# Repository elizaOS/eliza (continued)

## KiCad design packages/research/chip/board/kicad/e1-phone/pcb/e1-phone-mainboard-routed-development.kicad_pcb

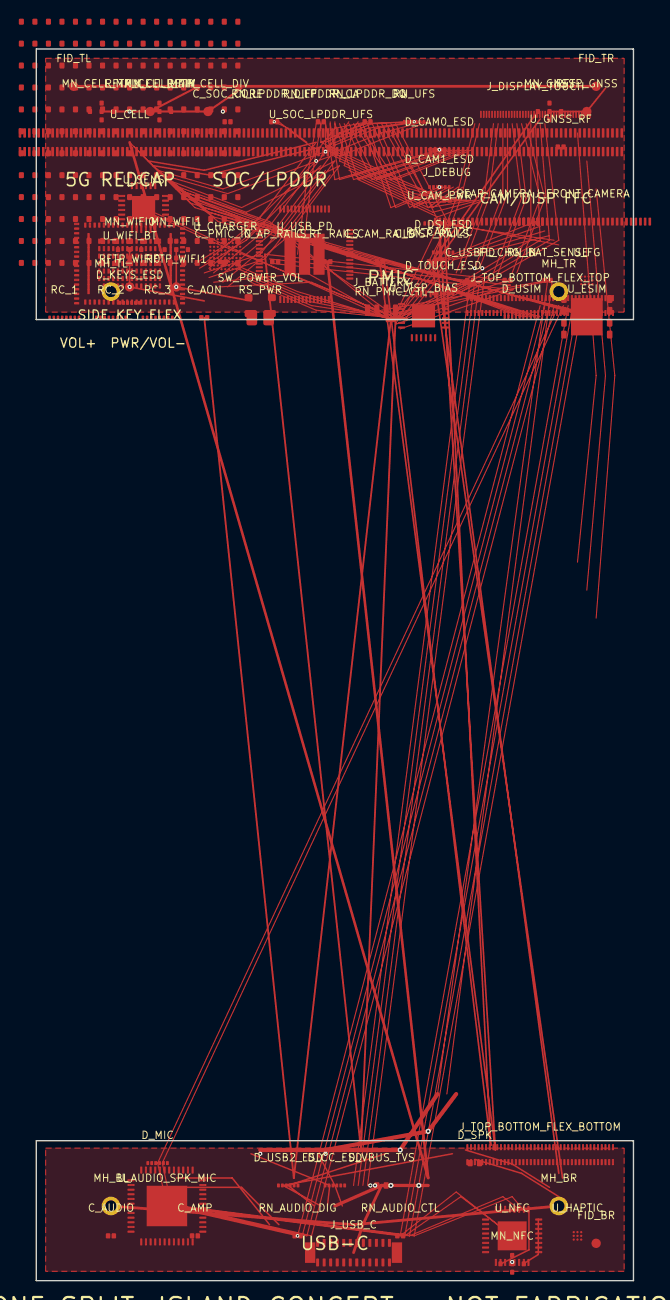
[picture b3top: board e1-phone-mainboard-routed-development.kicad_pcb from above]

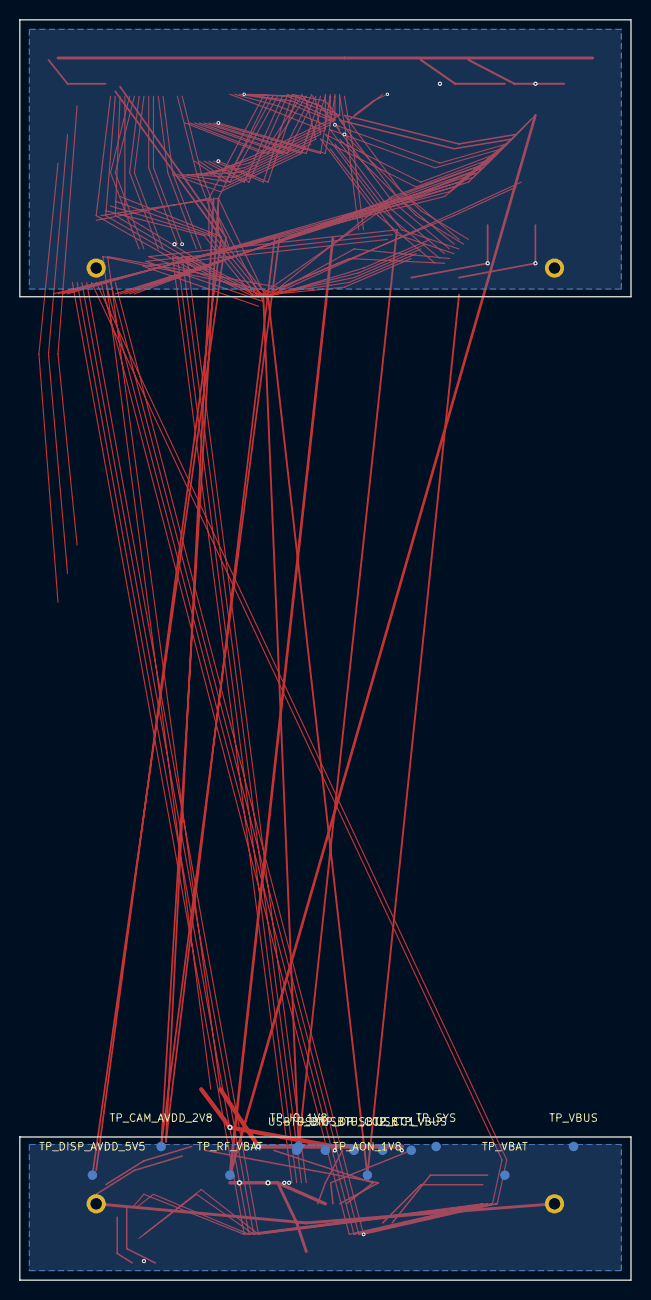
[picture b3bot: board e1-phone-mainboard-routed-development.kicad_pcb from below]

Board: 10 copper layers, 64.0 x 132.0 mm, 89 parts (13 on the bottom side), 109 nets.

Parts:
C_AMP: SMART_AMP_RAIL_DECOUPLING; C0402_DEV
C_AON: AON_BUTTON_WAKE_DECOUPLING; C0402_DEV
C_AP_RAILS: AP_CORE_IO_DECOUPLING; C0402_DEV
C_AUDIO: AUDIO_CODEC_RAIL_DECOUPLING; C0402_DEV
C_CAM_RAILS: CAMERA_AVDD_DVDD_DECOUPLING; C0402_DEV
C_DISP_RAILS: DISPLAY_BIAS_DECOUPLING; C0402_DEV
C_PMIC_IN: PMIC_SYS_VBAT_INPUT_DECOUPLING; C0402_DEV
C_RF_RAILS: RF_VBAT_IO_DECOUPLING; C0402_DEV
C_SOC_CORE: SOC_CORE_IO_DECOUPLING; C0402_DEV
C_USBPD: USBPD_VIN_DECOUPLING; C0402_DEV
D_CAM0_ESD: CAM0_CSI_ESD_ARRAY; ESD_ARRAY_6CH_DEV
D_CAM1_ESD: CAM1_CSI_ESD_ARRAY; ESD_ARRAY_6CH_DEV
D_CC_ESD: CC_ESD_ARRAY; ESD_ARRAY_6CH_DEV
D_DSI_ESD: DSI_4LANE_ESD_ARRAY; ESD_ARRAY_6CH_DEV
D_KEYS_ESD: SIDE_KEY_ESD_ARRAY; ESD_ARRAY_6CH_DEV
D_MIC: PDM_MIC_ESD_BIAS_DEVELOPMENT_PATTERN; ESD_ARRAY_6CH_DEV
D_SPK: SPEAKER_OUTPUT_PROTECT; TVS_DIODE_2P_DEV
D_TOUCH_ESD: TOUCH_CONTROL_ESD; ESD_ARRAY_6CH_DEV
D_USB2_ESD: USB2_ESD_ARRAY; ESD_ARRAY_6CH_DEV
D_USIM: USIM_ESD_LEVEL_SHIFT_DEVELOPMENT_PATTERN; USIM_ESD_LEVELSHIFT_DEV
D_VBUS_TVS: VBUS_TVS; TVS_DIODE_2P_DEV
FID_BR: FIDUCIAL; FIDUCIAL_1MM_DEV
FID_TL: FIDUCIAL; FIDUCIAL_1MM_DEV
FID_TR: FIDUCIAL; FIDUCIAL_1MM_DEV
FL_CHG_IN: VBUS_CHARGER_INPUT_FILTER; C0402_DEV
J_BATTERY: battery_pack_power_thermistor_id; BATTERY_4P_1P00_DEV
J_DEBUG: JTAG_BOOT_STRAP_TEST_ACCESS; R0402_DEV
J_DISPLAY_TOUCH: 5p5_in_fhd_mipi_display_touch_fpc_connector_escape; DISPLAY_40P_0P30_DEV
J_FRONT_CAMERA: 30-pin front MIPI CSI camera FPC development conn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; CAMERA_30P_0P50_DEV
J_REAR_CAMERA: 24-pin rear MIPI CSI camera FPC development conne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; CAMERA_24P_0P50_DEV
J_TOP_BOTTOM_FLEX_BOTTOM: bottom_mate_for_split_board_interconnect; HIROSE_DF40_80P_0P4_DEV
J_TOP_BOTTOM_FLEX_TOP: top_mate_for_split_board_interconnect; HIROSE_DF40_80P_0P4_DEV
J_USB_C: charging_data_debug_single_usb_c_port; GCT_USB4105_GF_A_DEV
MH_BL: MOUNT; MOUNTING_HOLE_1P2_DEV
MH_BR: MOUNT; MOUNTING_HOLE_1P2_DEV
MH_TL: MOUNT; MOUNTING_HOLE_1P2_DEV
MH_TR: MOUNT; MOUNTING_HOLE_1P2_DEV
MN_CELL_DIV: CELL_RF_DIV_PI_MATCH; PI_MATCH_0402_DEV
MN_CELL_MAIN: CELL_RF_MAIN_PI_MATCH; PI_MATCH_0402_DEV
MN_GNSS: CELL_GNSS_RF_PI_MATCH; PI_MATCH_0402_DEV
MN_NFC: NFC_LOOP_MATCH_DEVELOPMENT_PATTERN; NFC_LOOP_MATCH_DEV
MN_WIFI0: WIFI_BT_RF0_PI_MATCH; PI_MATCH_0402_DEV
MN_WIFI1: WIFI_BT_RF1_PI_MATCH; PI_MATCH_0402_DEV
RC_1: PWR_KEY_N_RC_DEBOUNCE; RC_ARRAY_4CH_DEV
RC_2: VOL_UP_N_RC_DEBOUNCE; RC_ARRAY_4CH_DEV
RC_3: VOL_DOWN_N_RC_DEBOUNCE; RC_ARRAY_4CH_DEV
RFTP_CELL_DIV: CELL_RF_DIV; TESTPOINT_1MM_DEV
RFTP_CELL_MAIN: CELL_RF_MAIN; TESTPOINT_1MM_DEV
RFTP_GNSS: CELL_GNSS_RF; TESTPOINT_1MM_DEV
RFTP_WIFI0: WIFI_BT_RF0; TESTPOINT_1MM_DEV
RFTP_WIFI1: WIFI_BT_RF1; TESTPOINT_1MM_DEV
RN_AUDIO_CTL: AUDIO_I2C_IRQ_PULLUPS; R0402_DEV
RN_AUDIO_DIG: I2S_PDM_DAMPING_DEVELOPMENT_PATTERN; R0402_DEV
RN_BAT_SENSE: BATTERY_NTC_ID_SENSE; R0402_DEV
RN_CAM_I2C: CAMERA_I2C_AF_PULLUPS; R0402_DEV
RN_LPDDR_CA: LPDDR_CA_DAMPING_DEVELOPMENT_PATTERN; R0402_DEV
RN_LPDDR_DIFF: LPDDR_CK_DQS_TERM_DEVELOPMENT_PATTERN; R0402_DEV
RN_LPDDR_DQ: LPDDR_DQ_ESCAPE_DEVELOPMENT_PATTERN; R0402_DEV
RN_PMIC_CTL: PMIC_CHARGER_PD_I2C_IRQ_PULLUPS; R0402_DEV
RN_UFS: UFS_MPHY_ESD_TERM_DEVELOPMENT_PATTERN; ESD_ARRAY_6CH_DEV
RS_PWR: VBUS_VBAT_SYS_CURRENT_SENSE; SHUNT_1206_DEV
SW_POWER_VOL: power_volume_side_key_flex_connector; PANASONIC_EVQ_P7_DEV
TP_AON_1V8: AON_1V8; TESTPOINT_1MM_DEV
TP_CAM_AVDD_2V8: CAM_AVDD_2V8; TESTPOINT_1MM_DEV
TP_DISP_AVDD_5V5: DISP_AVDD_5V5; TESTPOINT_1MM_DEV
TP_IO_1V8: IO_1V8; TESTPOINT_1MM_DEV
TP_RF_VBAT: RF_VBAT; TESTPOINT_1MM_DEV
TP_SYS: SYS; TESTPOINT_1MM_DEV
TP_VBAT: VBAT; TESTPOINT_1MM_DEV
TP_VBUS: VBUS; TESTPOINT_1MM_DEV
USBTP_CC1: USB_CC1; TESTPOINT_1MM_DEV
USBTP_CC2: USB_CC2; TESTPOINT_1MM_DEV
USBTP_DN: USB_DN; TESTPOINT_1MM_DEV
USBTP_DP: USB_DP; TESTPOINT_1MM_DEV
USBTP_VBUS: VBUS; TESTPOINT_1MM_DEV
U_AUDIO_SPK_MIC: bottom_left_audio_codec_speaker_microphone_haptic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; AUDIO_CODEC_QFN48_DEV
U_CAM_PWR: CAMERA_POWER_SEQUENCE_DEVELOPMENT_PATTERN; RC_ARRAY_4CH_DEV
U_CELL: cellular_5g_redcap_module; QUECTEL_RG255C_GEOMETRY_DEV
U_CHARGER: MAX77860 charger/power-path development package; ADI_MAX77860_WLP81_DEV
U_DISP_BIAS: DISPLAY_BIAS_BACKLIGHT_DEVELOPMENT_PATTERN; BACKLIGHT_BIAS_POWER_DEV
U_ESIM: ESIM_MODULE_DEVELOPMENT_PATTERN; ESIM_LGA_DEV
U_FG: FUEL_GAUGE_DEVELOPMENT_PATTERN; FUEL_GAUGE_WLCSP_DEV
U_GNSS_RF: GNSS_LNA_SAW_DEVELOPMENT_PATTERN; L0402_DEV
U_HAPTIC: HAPTIC_DRIVER_DEVELOPMENT_PATTERN; HAPTIC_DRIVER_WLCSP_DEV
U_NFC: NFC_CONTROLLER_DEVELOPMENT_PATTERN; NFC_CONTROLLER_QFN_DEV
U_SENS: IMU_ALS_PROX_BARO_DEVELOPMENT_PATTERN; SENSOR_HUB_QFN_DEV
U_SOC_LPDDR_UFS: compute_memory_storage; SODIMM_260P_0P5_COMPUTE_SOM_DEV
U_USB_PD: TPS65987 USB-PD controller development package; TI_TPS65987_RSH_56QFN_DEV
U_WIFI_BT: wifi_6e_bluetooth_module; MURATA_TYPE_2EA_GEOMETRY_DEV

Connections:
AMP_INT: J_TOP_BOTTOM_FLEX_BOTTOM.B19, J_TOP_BOTTOM_FLEX_TOP.B19, U_AUDIO_SPK_MIC.16
AON_1V8: C_AON.1, D_KEYS_ESD.4, J_TOP_BOTTOM_FLEX_BOTTOM.A8, J_TOP_BOTTOM_FLEX_TOP.A8, RC_1.4, RC_2.4, RC_3.4, TP_AON_1V8.1, U_NFC.1, U_SENS.1
AUDIO_I2C_SCL: J_TOP_BOTTOM_FLEX_BOTTOM.A18, J_TOP_BOTTOM_FLEX_TOP.A18, RN_AUDIO_CTL.1, U_AUDIO_SPK_MIC.4
AUDIO_I2C_SDA: J_TOP_BOTTOM_FLEX_BOTTOM.B18, J_TOP_BOTTOM_FLEX_TOP.B18, U_AUDIO_SPK_MIC.5
BAT_ID: J_BATTERY.3, U_CHARGER.E7, U_FG.A4
BAT_NTC: J_BATTERY.2, RN_BAT_SENSE.1, U_CHARGER.A2, U_CHARGER.B1, U_FG.A3
BOOT_MODE0: J_DEBUG.1, U_SOC_LPDDR_UFS.B76
BT_EN: U_SOC_LPDDR_UFS.A98, U_WIFI_BT.45
CAM0_CSI_CLK_N: D_CAM0_ESD.2, J_REAR_CAMERA.8, U_SOC_LPDDR_UFS.B33
CAM0_CSI_CLK_P: D_CAM0_ESD.1, J_REAR_CAMERA.7, U_SOC_LPDDR_UFS.B34
CAM0_CSI_D0_N: D_CAM0_ESD.4, J_REAR_CAMERA.10, U_SOC_LPDDR_UFS.A29
CAM0_CSI_D0_P: D_CAM0_ESD.3, J_REAR_CAMERA.9, U_SOC_LPDDR_UFS.A30
CAM0_CSI_D1_N: D_CAM0_ESD.6, J_REAR_CAMERA.13, U_SOC_LPDDR_UFS.A27
CAM0_CSI_D1_P: D_CAM0_ESD.5, J_REAR_CAMERA.12, U_SOC_LPDDR_UFS.A28
CAM0_CSI_D2_N: J_REAR_CAMERA.15, U_SOC_LPDDR_UFS.A25
CAM0_CSI_D2_P: J_REAR_CAMERA.14, U_SOC_LPDDR_UFS.A26
CAM0_CSI_D3_N: J_REAR_CAMERA.18, U_SOC_LPDDR_UFS.A23
CAM0_CSI_D3_P: J_REAR_CAMERA.17, U_SOC_LPDDR_UFS.A24
CAM0_I2C_SCL: J_REAR_CAMERA.21, RN_CAM_I2C.1, U_SOC_LPDDR_UFS.B54
CAM0_I2C_SDA: J_REAR_CAMERA.22, U_SOC_LPDDR_UFS.B55
CAM0_MCLK: J_REAR_CAMERA.5, U_CAM_PWR.5, U_SOC_LPDDR_UFS.A1
CAM0_PWDN: J_REAR_CAMERA.20, U_CAM_PWR.3
CAM0_RESET_N: J_REAR_CAMERA.19, U_CAM_PWR.1, U_SOC_LPDDR_UFS.B10
CAM1_CSI_CLK_N: D_CAM1_ESD.2, J_FRONT_CAMERA.8, U_SOC_LPDDR_UFS.B30
CAM1_CSI_CLK_P: D_CAM1_ESD.1, J_FRONT_CAMERA.7, U_SOC_LPDDR_UFS.B31
CAM1_CSI_D0_N: D_CAM1_ESD.4, J_FRONT_CAMERA.10
CAM1_CSI_D0_P: D_CAM1_ESD.3, J_FRONT_CAMERA.9
CAM1_CSI_D1_N: D_CAM1_ESD.6, J_FRONT_CAMERA.13
CAM1_CSI_D1_P: D_CAM1_ESD.5, J_FRONT_CAMERA.12
CAM1_MCLK: J_FRONT_CAMERA.5, U_SOC_LPDDR_UFS.A11
CAM1_RESET_N: J_FRONT_CAMERA.15, U_SOC_LPDDR_UFS.A16
CAM_AFVDD_2V8: J_FRONT_CAMERA.19, J_REAR_CAMERA.23
CAM_AVDD_2V8: C_CAM_RAILS.1, J_FRONT_CAMERA.2, J_FRONT_CAMERA.22, J_REAR_CAMERA.2, TP_CAM_AVDD_2V8.1, U_CAM_PWR.7
CAM_DVDD_1V2: J_FRONT_CAMERA.3, J_FRONT_CAMERA.23, J_REAR_CAMERA.3
CELL_GNSS_RF: MN_GNSS.1, MN_GNSS.2, MN_GNSS.3, RFTP_GNSS.1, U_CELL.51, U_GNSS_RF.1
CELL_PCIE_RX_N: U_CELL.102, U_SOC_LPDDR_UFS.A71
CELL_PCIE_RX_P: U_CELL.101, U_SOC_LPDDR_UFS.A70
CELL_PCIE_TX_N: U_CELL.104, U_SOC_LPDDR_UFS.A75
CELL_PCIE_TX_P: U_CELL.103, U_SOC_LPDDR_UFS.A76
CELL_RESET_N: U_CELL.20, U_CELL.24, U_SOC_LPDDR_UFS.A105
CELL_RF_DIV: MN_CELL_DIV.1, MN_CELL_DIV.2, MN_CELL_DIV.3, RFTP_CELL_DIV.1, U_CELL.39
CELL_RF_MAIN: MN_CELL_MAIN.1, MN_CELL_MAIN.2, MN_CELL_MAIN.3, RFTP_CELL_MAIN.1, U_CELL.55
CELL_USB2_DN: U_CELL.76, U_SOC_LPDDR_UFS.A5
CELL_USB2_DP: U_CELL.75, U_SOC_LPDDR_UFS.A6
CHG_I2C_SCL: U_CHARGER.E9, U_FG.B1, U_USB_PD.27
CHG_I2C_SDA: U_CHARGER.F9, U_FG.B2, U_USB_PD.28
CHG_IRQ_N: U_CHARGER.C7, U_CHARGER.D8, U_CHARGER.E6
CODEC_INT: J_TOP_BOTTOM_FLEX_BOTTOM.A19, J_TOP_BOTTOM_FLEX_TOP.A19, U_AUDIO_SPK_MIC.6
DISP_AVDD_5V5: C_DISP_RAILS.1, J_DISPLAY_TOUCH.2, J_DISPLAY_TOUCH.28, TP_DISP_AVDD_5V5.1, U_DISP_BIAS.1
DISP_AVEE_N5V5: J_DISPLAY_TOUCH.3, J_DISPLAY_TOUCH.29, U_DISP_BIAS.2
DISP_BL_EN: J_DISPLAY_TOUCH.20, J_DISPLAY_TOUCH.31, U_DISP_BIAS.3, U_SOC_LPDDR_UFS.A63, U_SOC_LPDDR_UFS.B60
DISP_BL_PWM: J_DISPLAY_TOUCH.21, J_DISPLAY_TOUCH.32, U_DISP_BIAS.4
DISP_RESET_N: J_DISPLAY_TOUCH.18, J_DISPLAY_TOUCH.38, U_SOC_LPDDR_UFS.B14
DISP_TE: J_DISPLAY_TOUCH.19, J_DISPLAY_TOUCH.39
DSI_CLK_N: D_DSI_ESD.2, J_DISPLAY_TOUCH.6, U_SOC_LPDDR_UFS.B45
DSI_CLK_P: D_DSI_ESD.1, J_DISPLAY_TOUCH.5, U_SOC_LPDDR_UFS.B46
DSI_D0_N: D_DSI_ESD.4, J_DISPLAY_TOUCH.9, U_SOC_LPDDR_UFS.A47
DSI_D0_P: D_DSI_ESD.3, J_DISPLAY_TOUCH.8, U_SOC_LPDDR_UFS.A48
DSI_D1_N: D_DSI_ESD.6, J_DISPLAY_TOUCH.11, U_SOC_LPDDR_UFS.A45
DSI_D1_P: D_DSI_ESD.5, J_DISPLAY_TOUCH.10, U_SOC_LPDDR_UFS.A46
DSI_D2_N: J_DISPLAY_TOUCH.14, U_SOC_LPDDR_UFS.A43
DSI_D2_P: J_DISPLAY_TOUCH.13, U_SOC_LPDDR_UFS.A44
DSI_D3_N: J_DISPLAY_TOUCH.16, U_SOC_LPDDR_UFS.A41
DSI_D3_P: J_DISPLAY_TOUCH.15, U_SOC_LPDDR_UFS.A42
GND: C_AMP.2, C_AON.2, C_AP_RAILS.2, C_AUDIO.2, C_CAM_RAILS.2, C_DISP_RAILS.2, C_PMIC_IN.2, C_RF_RAILS.2, C_SOC_CORE.2, C_USBPD.2, D_CC_ESD.3, D_CC_ESD.4, D_KEYS_ESD.5, D_KEYS_ESD.6, D_MIC.4, D_TOUCH_ESD.5, D_USB2_ESD.3, D_USB2_ESD.4, D_USIM.6, D_VBUS_TVS.2, FL_CHG_IN.2, J_BATTERY.4, J_DEBUG.2, J_DISPLAY_TOUCH.1, J_DISPLAY_TOUCH.7, J_DISPLAY_TOUCH.12, J_DISPLAY_TOUCH.17, J_DISPLAY_TOUCH.26, J_DISPLAY_TOUCH.30, J_DISPLAY_TOUCH.33, J_DISPLAY_TOUCH.36, J_DISPLAY_TOUCH.40, J_FRONT_CAMERA.1, J_FRONT_CAMERA.6, J_FRONT_CAMERA.11, J_FRONT_CAMERA.14, J_FRONT_CAMERA.20, J_FRONT_CAMERA.21, J_REAR_CAMERA.1, J_REAR_CAMERA.6, J_REAR_CAMERA.11, J_REAR_CAMERA.16, J_REAR_CAMERA.24, J_TOP_BOTTOM_FLEX_BOTTOM.A1, J_TOP_BOTTOM_FLEX_BOTTOM.A5, J_TOP_BOTTOM_FLEX_BOTTOM.A6, J_TOP_BOTTOM_FLEX_BOTTOM.A7, J_TOP_BOTTOM_FLEX_BOTTOM.A11, J_TOP_BOTTOM_FLEX_BOTTOM.A12, J_TOP_BOTTOM_FLEX_BOTTOM.A13, J_TOP_BOTTOM_FLEX_BOTTOM.A14, J_TOP_BOTTOM_FLEX_BOTTOM.A16, J_TOP_BOTTOM_FLEX_BOTTOM.A17, J_TOP_BOTTOM_FLEX_BOTTOM.A24, J_TOP_BOTTOM_FLEX_BOTTOM.A25, J_TOP_BOTTOM_FLEX_BOTTOM.B2, J_TOP_BOTTOM_FLEX_BOTTOM.B8, J_TOP_BOTTOM_FLEX_BOTTOM.B9, J_TOP_BOTTOM_FLEX_BOTTOM.B20, J_TOP_BOTTOM_FLEX_BOTTOM.B24, J_TOP_BOTTOM_FLEX_TOP.A1, J_TOP_BOTTOM_FLEX_TOP.A5, J_TOP_BOTTOM_FLEX_TOP.A6, J_TOP_BOTTOM_FLEX_TOP.A7, J_TOP_BOTTOM_FLEX_TOP.A11, J_TOP_BOTTOM_FLEX_TOP.A12, J_TOP_BOTTOM_FLEX_TOP.A13, J_TOP_BOTTOM_FLEX_TOP.A14, J_TOP_BOTTOM_FLEX_TOP.A16, J_TOP_BOTTOM_FLEX_TOP.A17, J_TOP_BOTTOM_FLEX_TOP.A24, J_TOP_BOTTOM_FLEX_TOP.A25, J_TOP_BOTTOM_FLEX_TOP.B2, J_TOP_BOTTOM_FLEX_TOP.B8, J_TOP_BOTTOM_FLEX_TOP.B9, J_TOP_BOTTOM_FLEX_TOP.B20, J_TOP_BOTTOM_FLEX_TOP.B24, J_USB_C.A1, J_USB_C.A12, J_USB_C.B1, J_USB_C.B12, J_USB_C.SH1, J_USB_C.SH2, MN_CELL_DIV.4, MN_CELL_DIV.5, MN_CELL_MAIN.4, MN_CELL_MAIN.5, MN_GNSS.4, MN_GNSS.5, MN_NFC.4, MN_NFC.5, MN_WIFI0.4, MN_WIFI0.5, MN_WIFI1.4, MN_WIFI1.5, RC_1.2, RC_2.2, RC_3.2, RN_BAT_SENSE.2, RN_UFS.5, RN_UFS.6, SW_POWER_VOL.4, U_AUDIO_SPK_MIC.3, U_CAM_PWR.2, U_CAM_PWR.6, U_CAM_PWR.8, U_CELL.10, U_CELL.11, U_CELL.12, U_CELL.23, U_CELL.26, U_CELL.33, U_CELL.35, U_CELL.38, U_CELL.40, U_CELL.50, U_CELL.52, U_CELL.54, U_CELL.56, U_CELL.57, U_CELL.58, U_CELL.59, U_CELL.60, U_CELL.62, U_CELL.78, U_CELL.109, U_CELL.115, U_CELL.125, U_CELL.126, U_CELL.135, U_CELL.137, U_CELL.140, U_CELL.141, U_CELL.143, U_CELL.149, U_CELL.151, U_CELL.163, U_CELL.169, U_CELL.170, U_CELL.171, U_CELL.172, U_CELL.173, U_CELL.174, U_CELL.175, U_CELL.176, U_CELL.177, U_CELL.178, U_CELL.179, U_CELL.180, U_CELL.181, U_CELL.182, U_CELL.183, U_CELL.184, U_CELL.185, U_CELL.186, U_CELL.187, U_CELL.188, U_CELL.189, U_CELL.190, U_CELL.191, U_CELL.192, U_CELL.193, U_CELL.194, U_CELL.195, U_CELL.196, U_CELL.197, U_CELL.198, U_CELL.199, U_CELL.200, U_CELL.201, U_CELL.202, U_CELL.203, U_CELL.204, U_CHARGER.A1, U_CHARGER.A3, U_CHARGER.A9, U_CHARGER.B6, U_CHARGER.B7, U_CHARGER.B8, U_CHARGER.B9, U_CHARGER.C4, U_CHARGER.C8, U_CHARGER.C9, U_CHARGER.D3, U_CHARGER.D4, U_CHARGER.D5, U_CHARGER.E5, U_CHARGER.F3, U_CHARGER.F4, U_CHARGER.G1, U_CHARGER.G2, U_CHARGER.H1, U_CHARGER.J1, U_CHARGER.J8, U_CHARGER.J9, U_DISP_BIAS.6, U_DISP_BIAS.7, U_DISP_BIAS.8, U_ESIM.1, U_ESIM.EP, U_FG.A2, U_GNSS_RF.2, U_HAPTIC.A3, U_HAPTIC.B2, U_NFC.3, U_SENS.3, U_SOC_LPDDR_UFS.A4, U_SOC_LPDDR_UFS.A7, U_SOC_LPDDR_UFS.A10, U_SOC_LPDDR_UFS.A22, U_SOC_LPDDR_UFS.A31, U_SOC_LPDDR_UFS.A40, U_SOC_LPDDR_UFS.A49, U_SOC_LPDDR_UFS.A58, U_SOC_LPDDR_UFS.B79, U_SOC_LPDDR_UFS.B86, U_SOC_LPDDR_UFS.B95, U_SOC_LPDDR_UFS.B111, U_SOC_LPDDR_UFS.B122, U_SOC_LPDDR_UFS.B123, U_SOC_LPDDR_UFS.B124, U_SOC_LPDDR_UFS.B125, U_USB_PD.20, U_USB_PD.45, U_USB_PD.46, U_USB_PD.47, U_USB_PD.51, U_USB_PD.59, U_WIFI_BT.4, U_WIFI_BT.9, U_WIFI_BT.15, U_WIFI_BT.20, U_WIFI_BT.21, U_WIFI_BT.23, U_WIFI_BT.25, U_WIFI_BT.29, U_WIFI_BT.31, U_WIFI_BT.36, U_WIFI_BT.38, U_WIFI_BT.39, U_WIFI_BT.42, U_WIFI_BT.46, U_WIFI_BT.47, U_WIFI_BT.48, U_WIFI_BT.49, U_WIFI_BT.50, U_WIFI_BT.52, U_WIFI_BT.54, U_WIFI_BT.56, U_WIFI_BT.59, U_WIFI_BT.67, U_WIFI_BT.70, U_WIFI_BT.73, U_WIFI_BT.76, U_WIFI_BT.77, U_WIFI_BT.78, U_WIFI_BT.79, U_WIFI_BT.80, U_WIFI_BT.81, U_WIFI_BT.82, U_WIFI_BT.83, U_WIFI_BT.84, U_WIFI_BT.85, U_WIFI_BT.86, U_WIFI_BT.87, U_WIFI_BT.88, U_WIFI_BT.89, U_WIFI_BT.90, U_WIFI_BT.91, U_WIFI_BT.92, U_WIFI_BT.93, U_WIFI_BT.94, U_WIFI_BT.95, U_WIFI_BT.98, U_WIFI_BT.103, U_WIFI_BT.104, U_WIFI_BT.107, U_WIFI_BT.108, U_WIFI_BT.111, U_WIFI_BT.112, U_WIFI_BT.113, U_WIFI_BT.115, U_WIFI_BT.116, U_WIFI_BT.117, U_WIFI_BT.118, U_WIFI_BT.119, U_WIFI_BT.120, U_WIFI_BT.121, U_WIFI_BT.122, U_WIFI_BT.123, U_WIFI_BT.124, U_WIFI_BT.132, U_WIFI_BT.133, U_WIFI_BT.135, U_WIFI_BT.136, U_WIFI_BT.137, U_WIFI_BT.138, U_WIFI_BT.139, U_WIFI_BT.140, U_WIFI_BT.141, U_WIFI_BT.142, U_WIFI_BT.143, U_WIFI_BT.144, U_WIFI_BT.145, U_WIFI_BT.146, U_WIFI_BT.147, U_WIFI_BT.148, U_WIFI_BT.149, U_WIFI_BT.150, U_WIFI_BT.151, U_WIFI_BT.152, U_WIFI_BT.153, U_WIFI_BT.154, U_WIFI_BT.155, U_WIFI_BT.156, U_WIFI_BT.157, U_WIFI_BT.158, U_WIFI_BT.159, U_WIFI_BT.160, U_WIFI_BT.161, U_WIFI_BT.162, U_WIFI_BT.163, U_WIFI_BT.164, U_WIFI_BT.165, U_WIFI_BT.166, U_WIFI_BT.167, U_WIFI_BT.168, U_WIFI_BT.169, U_WIFI_BT.170, U_WIFI_BT.171, U_WIFI_BT.172, U_WIFI_BT.173, U_WIFI_BT.174, U_WIFI_BT.175, U_WIFI_BT.176, U_WIFI_BT.177, U_WIFI_BT.178, U_WIFI_BT.179, U_WIFI_BT.180, U_WIFI_BT.181, U_WIFI_BT.182, U_WIFI_BT.183, U_WIFI_BT.184, U_WIFI_BT.185, U_WIFI_BT.186, U_WIFI_BT.187, U_WIFI_BT.188, U_WIFI_BT.189, U_WIFI_BT.190, U_WIFI_BT.191, U_WIFI_BT.192, U_WIFI_BT.193, U_WIFI_BT.194, U_WIFI_BT.195, U_WIFI_BT.196, U_WIFI_BT.197, U_WIFI_BT.198, U_WIFI_BT.199
HAPTIC_OUT: J_TOP_BOTTOM_FLEX_BOTTOM.A20, J_TOP_BOTTOM_FLEX_TOP.A20, U_AUDIO_SPK_MIC.17, U_HAPTIC.B1
I2S_BCLK: J_TOP_BOTTOM_FLEX_BOTTOM.B13, J_TOP_BOTTOM_FLEX_TOP.B13, RN_AUDIO_DIG.1, RN_AUDIO_DIG.2, U_AUDIO_SPK_MIC.7
I2S_DIN: J_TOP_BOTTOM_FLEX_BOTTOM.B15, J_TOP_BOTTOM_FLEX_TOP.B15, U_AUDIO_SPK_MIC.10
I2S_DOUT: J_TOP_BOTTOM_FLEX_BOTTOM.A15, J_TOP_BOTTOM_FLEX_TOP.A15, U_AUDIO_SPK_MIC.9
I2S_LRCLK: J_TOP_BOTTOM_FLEX_BOTTOM.B14, J_TOP_BOTTOM_FLEX_TOP.B14, U_AUDIO_SPK_MIC.8
IMU_INT: U_SENS.6, U_SOC_LPDDR_UFS.A12
IO_1V8: D_MIC.3, D_TOUCH_ESD.6, D_USIM.7, J_DISPLAY_TOUCH.4, J_DISPLAY_TOUCH.27, J_DISPLAY_TOUCH.37, J_FRONT_CAMERA.4, J_FRONT_CAMERA.24, J_REAR_CAMERA.4, J_TOP_BOTTOM_FLEX_BOTTOM.A9, J_TOP_BOTTOM_FLEX_TOP.A9, RN_AUDIO_CTL.2, RN_CAM_I2C.2, RN_PMIC_CTL.2, TP_IO_1V8.1, U_AUDIO_SPK_MIC.2, U_CAM_PWR.4, U_CELL.7, U_CHARGER.E8, U_CHARGER.F5, U_CHARGER.G4, U_DISP_BIAS.5, U_HAPTIC.A2, U_NFC.2, U_SENS.2, U_SOC_LPDDR_UFS.B112, U_SOC_LPDDR_UFS.B114, U_USB_PD.35, U_WIFI_BT.55
NFC_RF_N: MN_NFC.3, U_NFC.9
NFC_RF_P: MN_NFC.1, MN_NFC.2, U_NFC.8
PDM_CLK: D_MIC.1, J_TOP_BOTTOM_FLEX_BOTTOM.B16, J_TOP_BOTTOM_FLEX_TOP.B16, U_AUDIO_SPK_MIC.11
PDM_DAT: D_MIC.2, J_TOP_BOTTOM_FLEX_BOTTOM.B17, J_TOP_BOTTOM_FLEX_TOP.B17, U_AUDIO_SPK_MIC.12
PMIC_I2C_SCL: RN_PMIC_CTL.1, U_USB_PD.32
PWR_KEY_N: D_KEYS_ESD.1, RC_1.1, RC_1.3, SW_POWER_VOL.1, U_SOC_LPDDR_UFS.A111
RF_VBAT: C_RF_RAILS.1, J_TOP_BOTTOM_FLEX_BOTTOM.B12, J_TOP_BOTTOM_FLEX_TOP.B12, TP_RF_VBAT.1, U_CELL.63, U_CELL.64, U_WIFI_BT.57, U_WIFI_BT.58
SHIELD_GND: J_TOP_BOTTOM_FLEX_BOTTOM.A3, J_TOP_BOTTOM_FLEX_TOP.A3
SOC_RESET_N: U_SOC_LPDDR_UFS.B109, U_USB_PD.29, U_USB_PD.44
SPK_N: D_SPK.2, U_AUDIO_SPK_MIC.15
SPK_P: D_SPK.1, U_AUDIO_SPK_MIC.14
SYS: C_PMIC_IN.1, J_TOP_BOTTOM_FLEX_BOTTOM.B6, J_TOP_BOTTOM_FLEX_BOTTOM.B7, J_TOP_BOTTOM_FLEX_TOP.B6, J_TOP_BOTTOM_FLEX_TOP.B7, RS_PWR.1, TP_SYS.1, U_AUDIO_SPK_MIC.18, U_CHARGER.D6, U_CHARGER.D9, U_CHARGER.E1, U_CHARGER.E2, U_CHARGER.E3, U_CHARGER.F1, U_CHARGER.F2, U_CHARGER.H2, U_CHARGER.H3, U_CHARGER.J2, U_CHARGER.J3, U_HAPTIC.A1, U_USB_PD.1, U_USB_PD.2, U_USB_PD.7, U_USB_PD.11, U_USB_PD.12, U_USB_PD.52, U_USB_PD.56, U_USB_PD.57
TOUCH_I2C_SCL: D_TOUCH_ESD.1, J_DISPLAY_TOUCH.22, J_DISPLAY_TOUCH.34, U_SOC_LPDDR_UFS.A13
TOUCH_I2C_SDA: D_TOUCH_ESD.2, J_DISPLAY_TOUCH.23, J_DISPLAY_TOUCH.35, U_SOC_LPDDR_UFS.A14
TOUCH_IRQ_N: D_TOUCH_ESD.3, J_DISPLAY_TOUCH.24, U_SOC_LPDDR_UFS.A64
TOUCH_RESET_N: D_TOUCH_ESD.4, J_DISPLAY_TOUCH.25, U_SOC_LPDDR_UFS.B13
USB_CC1: D_CC_ESD.1, J_TOP_BOTTOM_FLEX_BOTTOM.B3, J_TOP_BOTTOM_FLEX_TOP.B3, J_USB_C.A5, USBTP_CC1.1, U_CHARGER.A6, U_USB_PD.24
USB_CC2: D_CC_ESD.2, J_TOP_BOTTOM_FLEX_BOTTOM.A4, J_TOP_BOTTOM_FLEX_TOP.A4, J_USB_C.B5, USBTP_CC2.1, U_CHARGER.A4, U_USB_PD.26
USB_DN: D_USB2_ESD.2, J_TOP_BOTTOM_FLEX_BOTTOM.A2, J_TOP_BOTTOM_FLEX_TOP.A2, J_USB_C.A7, J_USB_C.B6, USBTP_DN.1, U_CHARGER.A7, U_SOC_LPDDR_UFS.A8, U_USB_PD.53
USB_DP: D_USB2_ESD.1, J_TOP_BOTTOM_FLEX_BOTTOM.B1, J_TOP_BOTTOM_FLEX_TOP.B1, J_USB_C.A6, J_USB_C.B7, USBTP_DP.1, U_CHARGER.A8, U_SOC_LPDDR_UFS.A9, U_USB_PD.50
VBAT: J_BATTERY.1, J_TOP_BOTTOM_FLEX_BOTTOM.B11, J_TOP_BOTTOM_FLEX_TOP.B11, RS_PWR.2, TP_VBAT.1, U_CELL.65, U_CELL.66, U_CHARGER.C1, U_CHARGER.C2, U_CHARGER.D1, U_CHARGER.D2, U_CHARGER.E4, U_FG.A1
VBUS: D_VBUS_TVS.1, FL_CHG_IN.1, J_TOP_BOTTOM_FLEX_BOTTOM.B4, J_TOP_BOTTOM_FLEX_BOTTOM.B5, J_TOP_BOTTOM_FLEX_TOP.B4, J_TOP_BOTTOM_FLEX_TOP.B5, J_USB_C.A4, J_USB_C.A9, J_USB_C.B4, J_USB_C.B9, TP_VBUS.1, USBTP_VBUS.1, U_CELL.77, U_CHARGER.A5, U_CHARGER.D7, U_CHARGER.F6, U_CHARGER.G3, U_CHARGER.G5, U_CHARGER.G6, U_CHARGER.H4, U_CHARGER.H5, U_CHARGER.H6, U_CHARGER.J4, U_CHARGER.J5, U_CHARGER.J6, U_CHARGER.J7, U_SOC_LPDDR_UFS.A73, U_USB_PD.3, U_USB_PD.4, U_USB_PD.8, U_USB_PD.13, U_USB_PD.14, U_USB_PD.15, U_USB_PD.19, U_USB_PD.25, U_USB_PD.58
VDD_AMP_3V3: C_AMP.1, J_TOP_BOTTOM_FLEX_BOTTOM.B10, J_TOP_BOTTOM_FLEX_TOP.B10, U_AUDIO_SPK_MIC.13
VDD_AUDIO_3V3: C_AUDIO.1, J_TOP_BOTTOM_FLEX_BOTTOM.A10, J_TOP_BOTTOM_FLEX_TOP.A10, U_AUDIO_SPK_MIC.1, U_SOC_LPDDR_UFS.B115
VIN_3V3: C_USBPD.1, U_USB_PD.5
VOL_DOWN_N: D_KEYS_ESD.3, RC_3.1, RC_3.3, SW_POWER_VOL.3
VOL_UP_N: D_KEYS_ESD.2, RC_2.1, RC_2.3, SW_POWER_VOL.2
WIFI_BT_RF0: MN_WIFI0.1, MN_WIFI0.2, MN_WIFI0.3, RFTP_WIFI0.1, U_WIFI_BT.24, U_WIFI_BT.30
WIFI_BT_RF1: MN_WIFI1.1, MN_WIFI1.2, MN_WIFI1.3, RFTP_WIFI1.1, U_WIFI_BT.22, U_WIFI_BT.37
WIFI_EN: U_SOC_LPDDR_UFS.A102, U_WIFI_BT.41, U_WIFI_BT.60
WIFI_HOST_WAKE: U_SOC_LPDDR_UFS.A103, U_WIFI_BT.43
WIFI_SDIO_CLK: U_SOC_LPDDR_UFS.B83, U_WIFI_BT.65
WIFI_SDIO_CMD: U_SOC_LPDDR_UFS.B82, U_WIFI_BT.64
WIFI_SDIO_D0: U_SOC_LPDDR_UFS.B84, U_WIFI_BT.62
WIFI_SDIO_D1: U_SOC_LPDDR_UFS.B85, U_WIFI_BT.63
WIFI_SDIO_D2: U_SOC_LPDDR_UFS.B80, U_WIFI_BT.61
WIFI_SDIO_D3: U_SOC_LPDDR_UFS.B81, U_WIFI_BT.66
